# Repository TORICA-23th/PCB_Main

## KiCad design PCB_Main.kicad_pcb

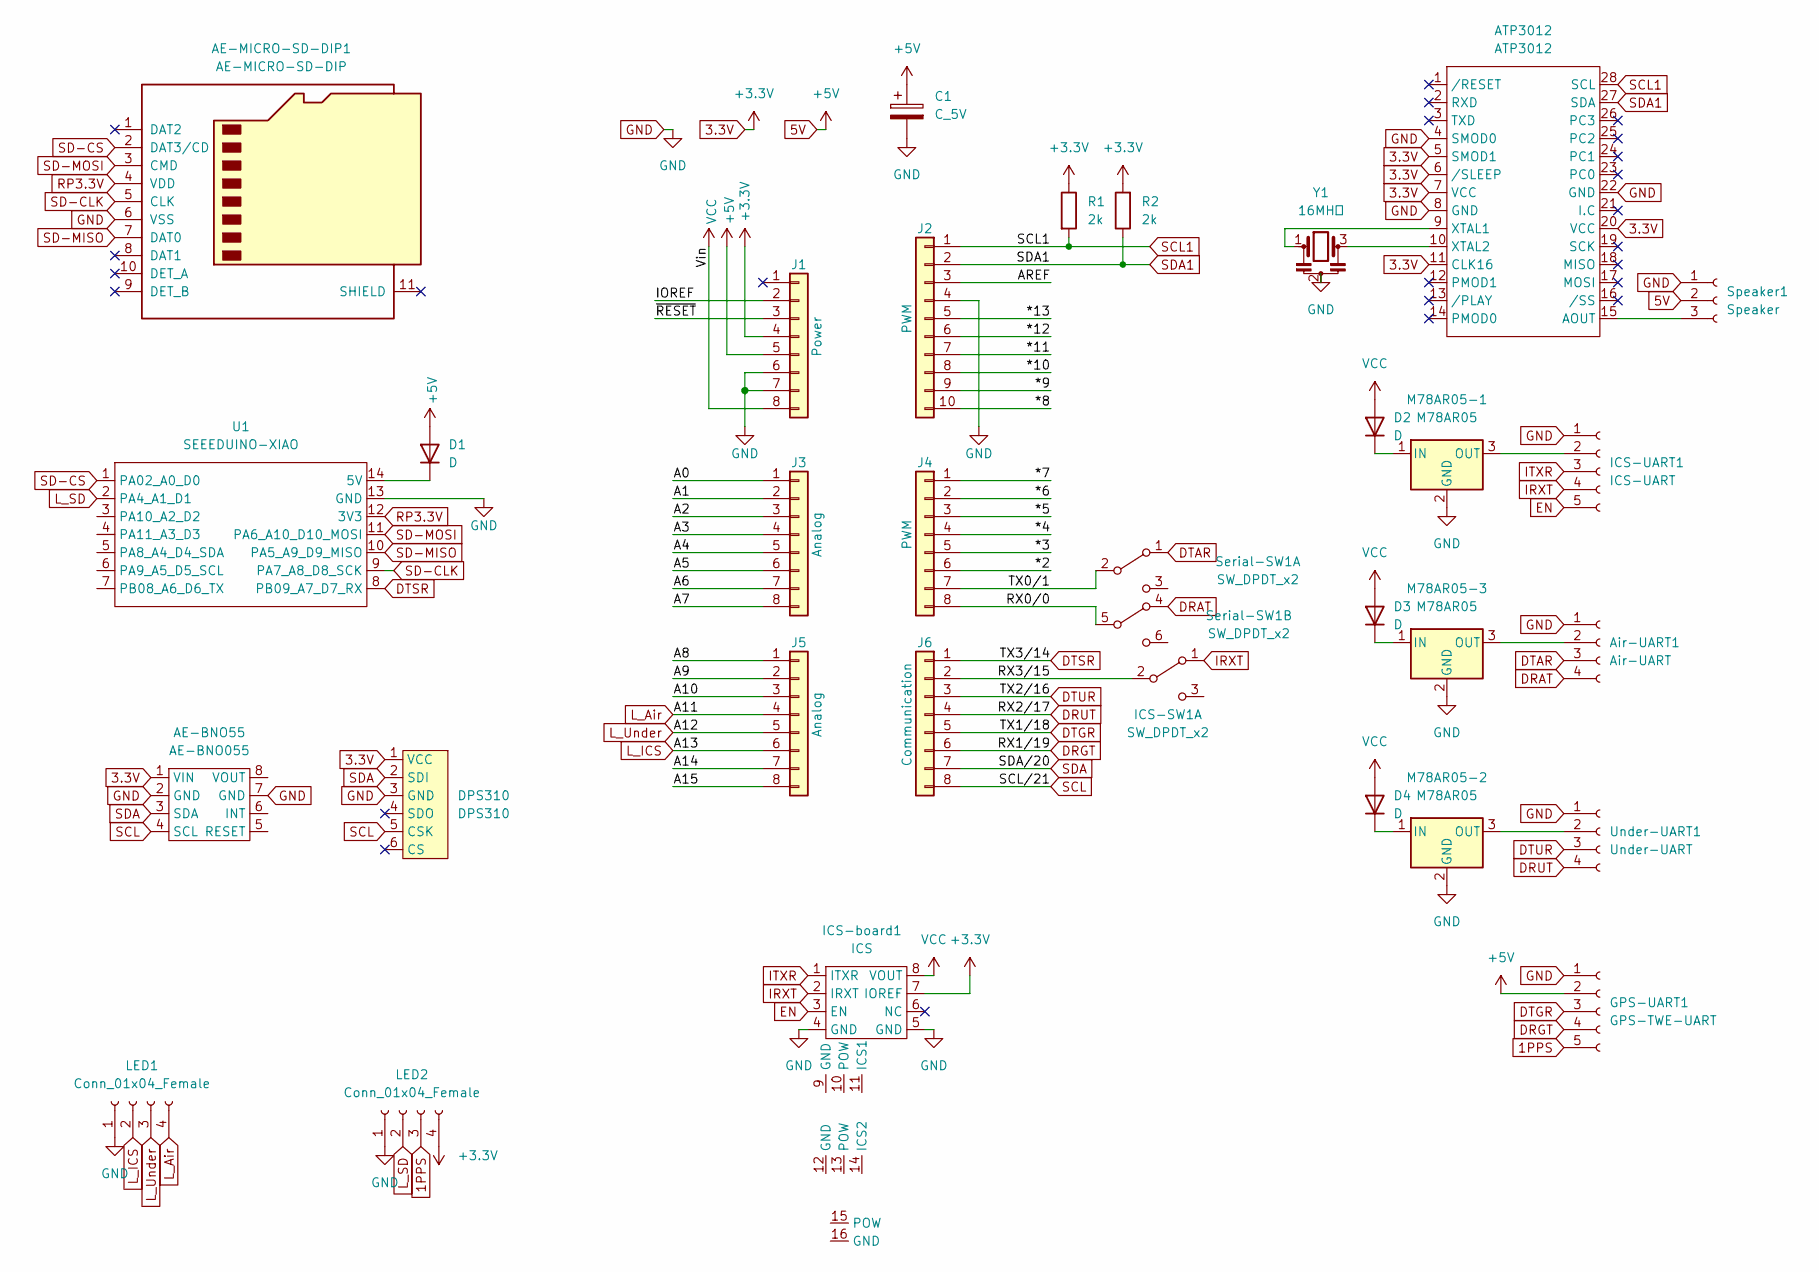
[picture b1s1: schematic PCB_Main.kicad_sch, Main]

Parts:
AE-BNO55: AE-BNO055
AE-MICRO-SD-DIP1: AE-MICRO-SD-DIP; microSD_AE-MICRO-SD-DIP
ATP3012: ATP3012; DIP-28_W7.62mm
Air-UART1: Air-UART; JST_XH_S4B-XH-A_1x04_P2.50mm_Horizontal
C1: C_5V; CP_Radial_D5.0mm_P2.50mm
D1: D; D_A-405_P12.70mm_Horizontal
D2, D3, D4: D; D_A-405_P10.16mm_Horizontal
DPS310: DPS310
GPS-UART1: GPS-TWE-UART; JST_XH_S5B-XH-A_1x05_P2.50mm_Horizontal
ICS-SW1: SW_DPDT_x2; PinHeader_1x03_P2.54mm_Vertical
ICS-UART1: ICS-UART; JST_XH_S5B-XH-A_1x05_P2.50mm_Horizontal
ICS-board1: ICS
J1: Power; PinHeader_1x08_P2.54mm_Vertical
J2: PWM; PinHeader_1x10_P2.54mm_Vertical
J3, J5: Analog; PinHeader_1x08_P2.54mm_Vertical
J4: PWM; PinHeader_1x08_P2.54mm_Vertical
J6: Communication; PinHeader_1x08_P2.54mm_Vertical
LED1, LED2: Conn_01x04_Female; JST_XH_S4B-XH-A_1x04_P2.50mm_Horizontal
M78AR05-1, M78AR05-2, M78AR05-3: M78AR05; Converter_DCDC_RECOM_R-78E-0.5_THT
R1, R2: 2k; R_Axial_DIN0204_L3.6mm_D1.6mm_P7.62mm_Horizontal
Serial-SW1: SW_DPDT_x2; SW_Push_2P2T_Toggle_CK_PVA2OAH5xxxxxxV2
Speaker1: Speaker; JST_XH_S3B-XH-A_1x03_P2.50mm_Horizontal
U1: SEEEDUINO-XIAO; MOUDLE14P-2.54-21X17.8MM
Under-UART1: Under-UART; JST_XH_S4B-XH-A_1x04_P2.50mm_Horizontal
Y1: 16MHｚ; Resonator_Murata_CSTLSxxxX-3Pin_W5.5mm_H3.0mm

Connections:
1PPS: GPS-UART1.5, LED2.3
3.3V: AE-BNO55.1 (VIN), ATP3012.5 (SMOD1), ATP3012.6 (/SLEEP), ATP3012.7 (VCC), ATP3012.11 (CLK16), ATP3012.20 (VCC), DPS310., DPS310.1 (VCC), ICS-board1.7 (IOREF), J1.4, LED2.4, R1.1, R2.2
5V: C1.1, D1.2 (A), GPS-UART1.2, J1.5, Speaker1.2
/*2: J4.6
/*3: J4.5
/*4: J4.4
/*5: J4.3
/*6: J4.2
/*7: J4.1
/*8: J2.10
/*9: J2.9
/*10: J2.8
/*11: J2.7
/*12: J2.6
/*13: J2.5
/A0: J3.1
/A1: J3.2
/A2: J3.3
/A3: J3.4
/A4: J3.5
/A5: J3.6
/A6: J3.7
/A7: J3.8
/A8: J5.1
/A9: J5.2
/A10: J5.3
/A14: J5.7
/A15: J5.8
/AREF: J2.3
/IOREF: J1.2
/RX0/0: J4.8, Serial-SW1.5 (B)
/RX3/15: ICS-SW1.2 (B), J6.2
/TX0/1: J4.7, Serial-SW1.2 (B)
/~RESET: J1.3
DRAT: Air-UART1.4, Serial-SW1.4 (A)
DRGT: GPS-UART1.4, J6.6
DRUT: J6.4, Under-UART1.4
DTAR: Air-UART1.3, Serial-SW1.1 (A)
DTGR: GPS-UART1.3, J6.5
DTSR: J6.1, U1.8 (PB09_A7_D7_RX)
DTUR: J6.3, Under-UART1.3
EN: ICS-UART1.5, ICS-board1.3 (EN)
GND: AE-BNO55.2 (GND), AE-BNO55.7 (GND), AE-MICRO-SD-DIP1.6 (VSS), ATP3012.4 (SMOD0), ATP3012.8 (GND), ATP3012.22 (GND), Air-UART1.1, C1.2, DPS310.3 (GND), GPS-UART1.1, ICS-UART1.1, ICS-board1.4 (GND), ICS-board1.5 (GND), J1.6, J1.7, J2.4, LED1.1, LED2.1, M78AR05-1.2 (GND), M78AR05-2.2 (GND), M78AR05-3.2 (GND), Speaker1.1, U1.13 (GND), Under-UART1.1, Y1.2
IRXT: ICS-SW1.1 (A), ICS-UART1.4, ICS-board1.2 (IRXT)
ITXR: ICS-UART1.3, ICS-board1.1 (ITXR)
L_Air: J5.4, LED1.4
L_ICS: J5.6, LED1.2
L_SD: LED2.2, U1.2 (PA4_A1_D1)
L_Under: J5.5, LED1.3
unnamed: ATP3012.9 (XTAL1), Y1.1
unnamed: ATP3012.10 (XTAL2), Y1.3
unnamed: ATP3012.15 (AOUT), Speaker1.3
unnamed: Air-UART1.2, M78AR05-3.3 (OUT)
unnamed: D1.1 (K), U1.14 (5V)
unnamed: D2.1 (K), M78AR05-1.1 (IN)
unnamed: D3.1 (K), M78AR05-3.1 (IN)
unnamed: D4.1 (K), M78AR05-2.1 (IN)
unnamed: ICS-UART1.2, M78AR05-1.3 (OUT)
unnamed: M78AR05-2.3 (OUT), Under-UART1.2
RP3.3V: AE-MICRO-SD-DIP1.4 (VDD), U1.12 (3V3)
SCL: AE-BNO55.4 (SCL), DPS310.5 (CSK), J6.8
SCL1: ATP3012.28 (SCL), J2.1, R1.2
SD-CLK: AE-MICRO-SD-DIP1.5 (CLK), U1.9 (PA7_A8_D8_SCK)
SD-CS: AE-MICRO-SD-DIP1.2 (DAT3/CD), U1.1 (PA02_A0_D0)
SD-MISO: AE-MICRO-SD-DIP1.7 (DAT0), U1.10 (PA5_A9_D9_MISO)
SD-MOSI: AE-MICRO-SD-DIP1.3 (CMD), U1.11 (PA6_A10_D10_MOSI)
SDA: AE-BNO55.3 (SDA), DPS310.2 (SDI), J6.7
SDA1: ATP3012.27 (SDA), J2.2, R2.1
VCC: D2.2 (A), D3.2 (A), D4.2 (A), ICS-board1.8 (VOUT), J1.8

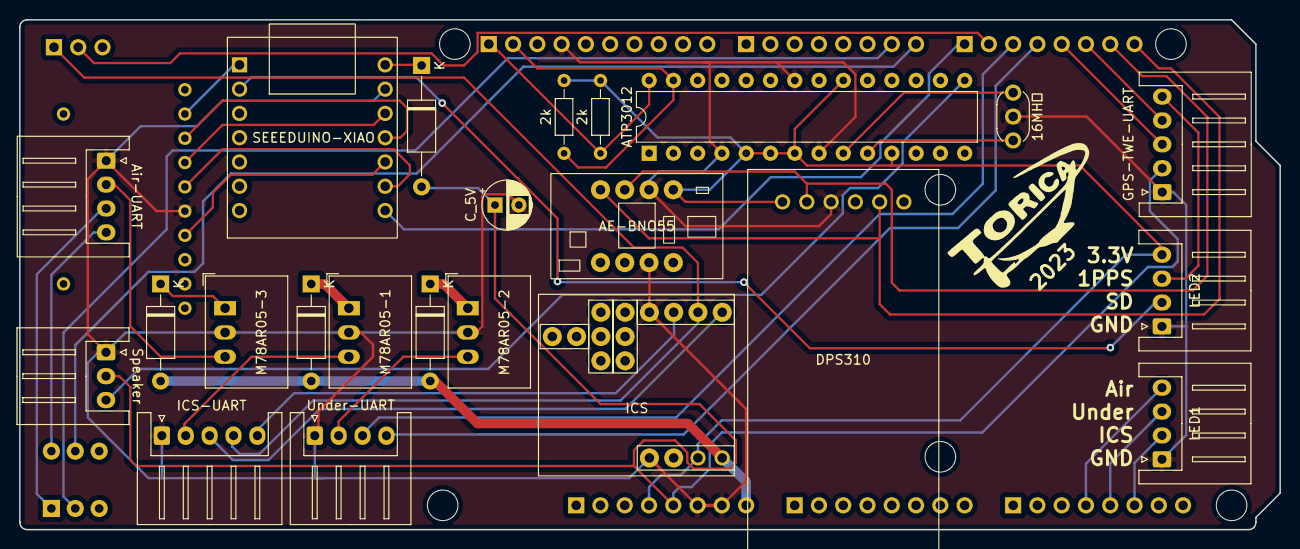
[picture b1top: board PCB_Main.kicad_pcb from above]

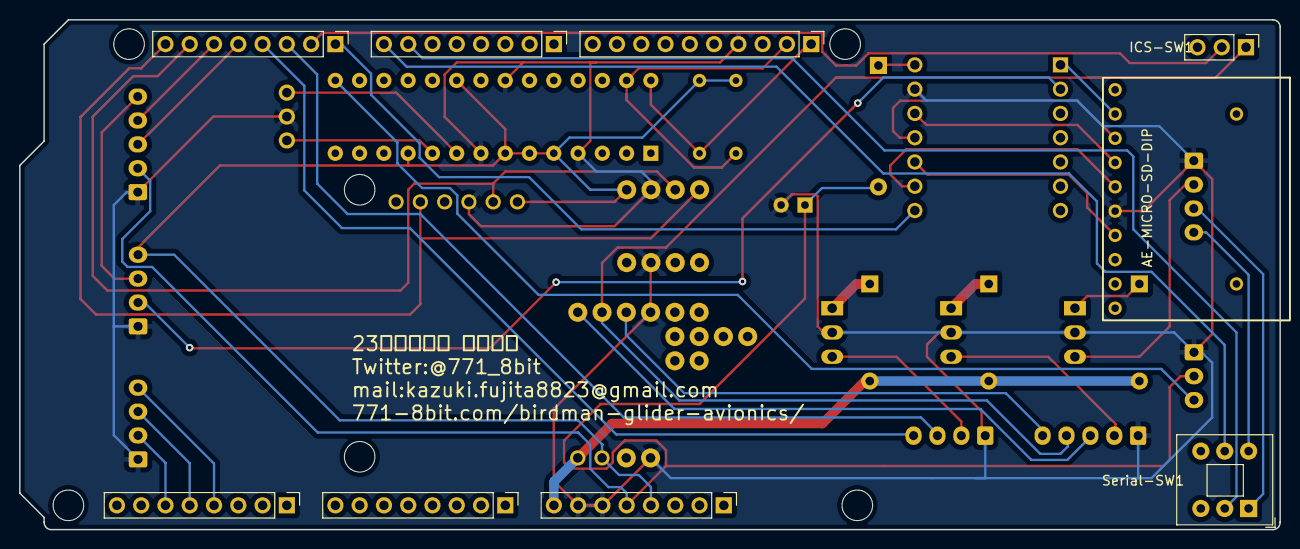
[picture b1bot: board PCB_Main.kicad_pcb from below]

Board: 2 copper layers, 131.9 x 53.3 mm, 38 parts (9 on the bottom side), 41 nets.

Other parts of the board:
MH1, MH2, MH3, MH4, MH5, MH6: MountingHole_3.2mm

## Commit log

2023-02-12 update silk
2023-02-12 pass DRC
2023-02-13 add capacitor
2023-06-09 jlcpcb
2024-03-18 Update all
2024-07-03 Organize 20240703
